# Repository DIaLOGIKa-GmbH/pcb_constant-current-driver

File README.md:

# LED Constant Current Driver Design

This project is part of [LibroDuct](https://www.libroduct.com/). We decided to publish some results of our LED driver designs to support the opensource maker scene. Feel free to use those results in your designs.

All those designs were tested with [9 IR-LEDs](https://jlcpcb.com/partdetail/Xssy-SE03_EMC3838AA60/C5205224) in series. These had a forward voltage of `14.0V`.

## LM3404 Constant Current Driver

The [LM3404 and LM3404HV](https://www.ti.com/lit/ds/symlink/lm3404.pdf) devices are monolithic switching regulators designed to deliver constant currents to high power LEDs. Ideal for automotive, industrial, and general lighting applications, these devices contain a high-side N-channel MOSFET switch with a current limit of 1.5A (typical) for step-down (Buck) regulators. Hysteretic controlled on-time and an external resistor allow the converter output voltage to adjust as needed to deliver a constant current to series and series-parallel connected LED arrays of varying number and type. 

_(LM3404 testing PCB render)_

The layout of the PCB closely resembles the recommended design shown in the datasheet.

_(LM3404 input and output current)_

As can be seen in this plot, the output current is not that stable when the input voltage is changed. This makes the chip unusable for applications with a varying input voltage.

_(LM3404 efficiency)_

TODO: Replace graph with better data. Chip seems to be quite efficient.

## AL8860 Constant Current Driver

The [AL8860](https://www.diodes.com/assets/Datasheets/AL8860.pdf) is a hysteresis mode DC-DC step-down converter, designed for driving single or multiple series connected LEDs efficiently from a voltage source higher than the LED voltage. The device can operate from an input supply between `4.5V` and `40V` and provide an externally adjustable output current up to `1A` for TSOT25 package and `1.5A` for MSOP-8EP package.

_(AL8860 testing PCB render)_

The curcuit designed is similar to the previous circuit but produces way better results thanks to the changed driving IC.

_(AL8860 input and output current)_

The above plot shows the input and output current. The output current is rather stable over the supported input voltage. This makes the circuit suitable for our needs.

It is also worth mentioning that the output current is a bit higher than the designed current. This is fine in our usecase but it is something to be aware of.

_(AL8860 driver efficiency at 700mA)_

### The Influence of Coil Selection

Another test we did with these drivers is so test and asses the influence of different coils on the efficiency. Especially the influence of the DC resistance.

_(AL8860 driver efficiency when tested with different coils)_

The above plot shows the same AL8860 driver that was used previously, but we added another coil in the mix. `v.A` uses a coil with a DC resistance of `98mΩ`, `v.B` has a DC resistance of `201mΩ`. The inductance of both coils is identical.

It can be seen that the efficiency drops with higher DC resistance as this energy is lost in the form of heat created. It is therefore reasonable to use a bigger and better coil if the space is not constrained.

### 1.5A Driver with AL8860MP

There is also an `1.5A` version available of the driving IC. I tested it as well and got really good results. It seems to be a bit more efficient than the `700mA` version. This could also be due to two LED strings being in parallel or the lower value of the shunt resistor.

_(AL8860MP driver efficiency at 1.5A)_

### Comparison

There are many off-the-shelf LED driver modules available. One of them, the [Meanwell LDD700LS](https://www.meanwell-web.com/content/files/pdfs/productPdfs/MW/LDD-l/ldd-l-spec.pdf) was used here as a refernce point. When supplied with `36V` at `700mA` and a LED forward voltage of `14V`, it seems to have an efficieny of `87%`. Even in our worst case scenario our driver is more efficient.

_(LDD700LS driver module efficiency [fig 3, page 4])_

### Trigger Signals

Since the dimming pin of most LED driver ICs is open drain with a limited voltage range, we need additional circuitry to get what we need. Also many ICs support analog dimming with values over 100% if the internal ref voltage is surpassed which forces us to use the internal pullup.

The following circuit achieves all of that, while also supporting trigger voltages as high as VCC of the LED board, while also making sure that pulling the input to ground still disables it.

By default this circuit turns the device on and has to be actively turned off.

_(PWM input modification schematic)_

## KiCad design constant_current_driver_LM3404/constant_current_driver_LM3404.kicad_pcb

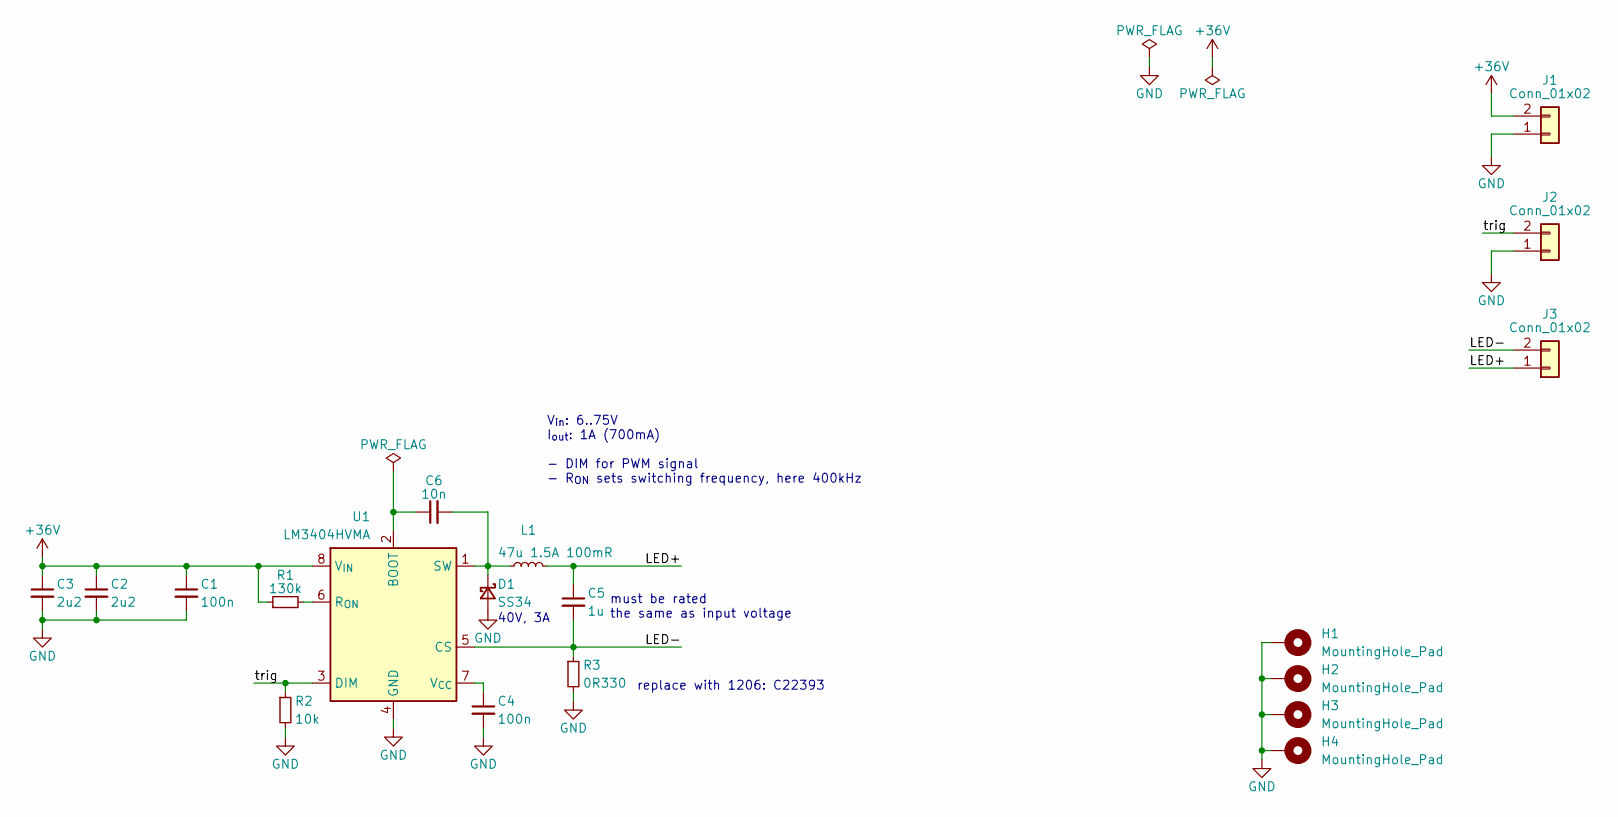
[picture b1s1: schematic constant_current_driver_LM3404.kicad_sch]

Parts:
C1, C4: 100n; C_0603_1608Metric; LCSC Part # C14663
C2, C3: 2u2; C_1206_3216Metric; LCSC Part # C50254
C5: 1u; C_1206_3216Metric; LCSC Part # C1848
C6: 10n; C_0603_1608Metric; LCSC Part # C57112
D1: SS34; D_SMA; LCSC Part # C8678
H1, H2, H3, H4: MountingHole_Pad; MountingHole_3.2mm_M3_Pad_TopOnly; LCSC Part # DNP
J1, J2, J3: Conn_01x02; TerminalBlock_Phoenix_MKDS-1,5-2-5.08_1x02_P5.08mm_Horizont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; LCSC Part # C8465
L1: 47u 1.5A 100mR; L_TDK_SLF10145; LCSC Part # C329816
R1: 130k; R_0603_1608Metric; LCSC Part # C22795
R2: 10k; R_0603_1608Metric; LCSC Part # C25804
R3: 0R330; R_0805_2012Metric; LCSC Part # C724024
U1: LM3404HVMA; SOIC-8_3.9x4.9mm_P1.27mm; LCSC Part # C1554286

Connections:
+36V: C1.1, C2.1, C3.1, J1.2, R1.1, U1.8 (V_{IN})
/LED+: C5.1, J3.1, L1.2
/LED-: C5.2, J3.2, R3.1, U1.5 (CS)
/trig: J2.2, R2.1, U1.3 (DIM)
GND: C1.2, C2.2, C3.2, C4.2, D1.2 (A), H1.1, H2.1, H3.1, H4.1, J1.1, J2.1, R2.2, R3.2, U1.4 (GND)
unnamed: C6.2, D1.1 (K), L1.1, U1.1 (SW)
unnamed: C6.1, U1.2 (BOOT)
unnamed: R1.2, U1.6 (R_{ON})
unnamed: C4.1, U1.7 (V_{CC})

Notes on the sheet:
must be rated the same as input voltage
40V, 3A
replace with 1206: C22393
V_{in}: 6..75V I_{out}: 1A (700mA) - DIM for PWM signal - R_{ON} sets switching frequency, here 400kHz

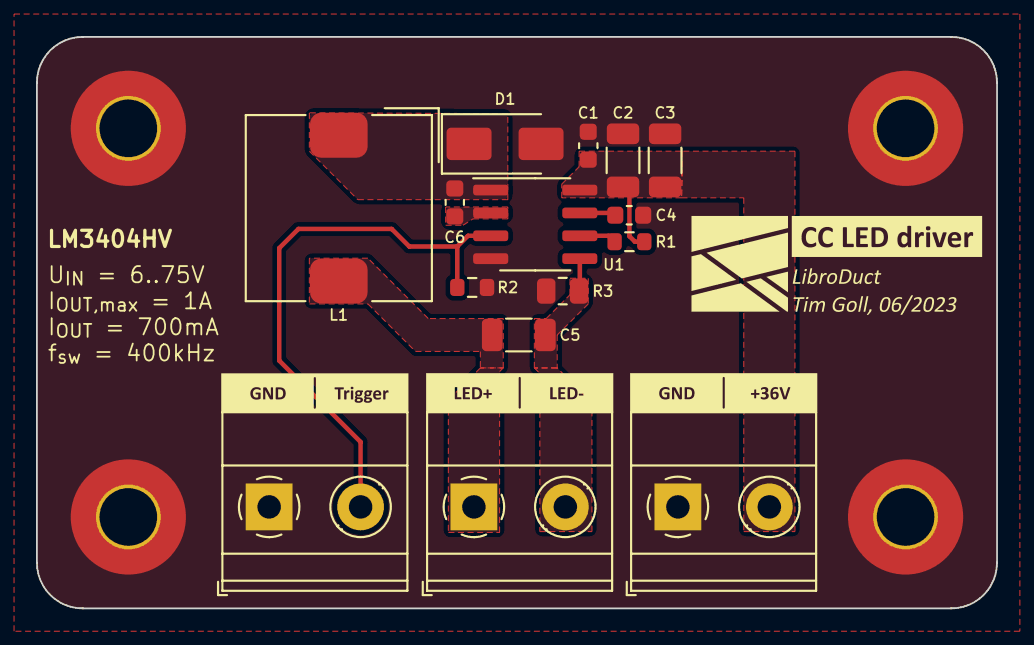
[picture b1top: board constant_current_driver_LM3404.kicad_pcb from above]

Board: 2 copper layers, 53.3 x 31.8 mm, 19 parts (0 on the bottom side), 9 nets.

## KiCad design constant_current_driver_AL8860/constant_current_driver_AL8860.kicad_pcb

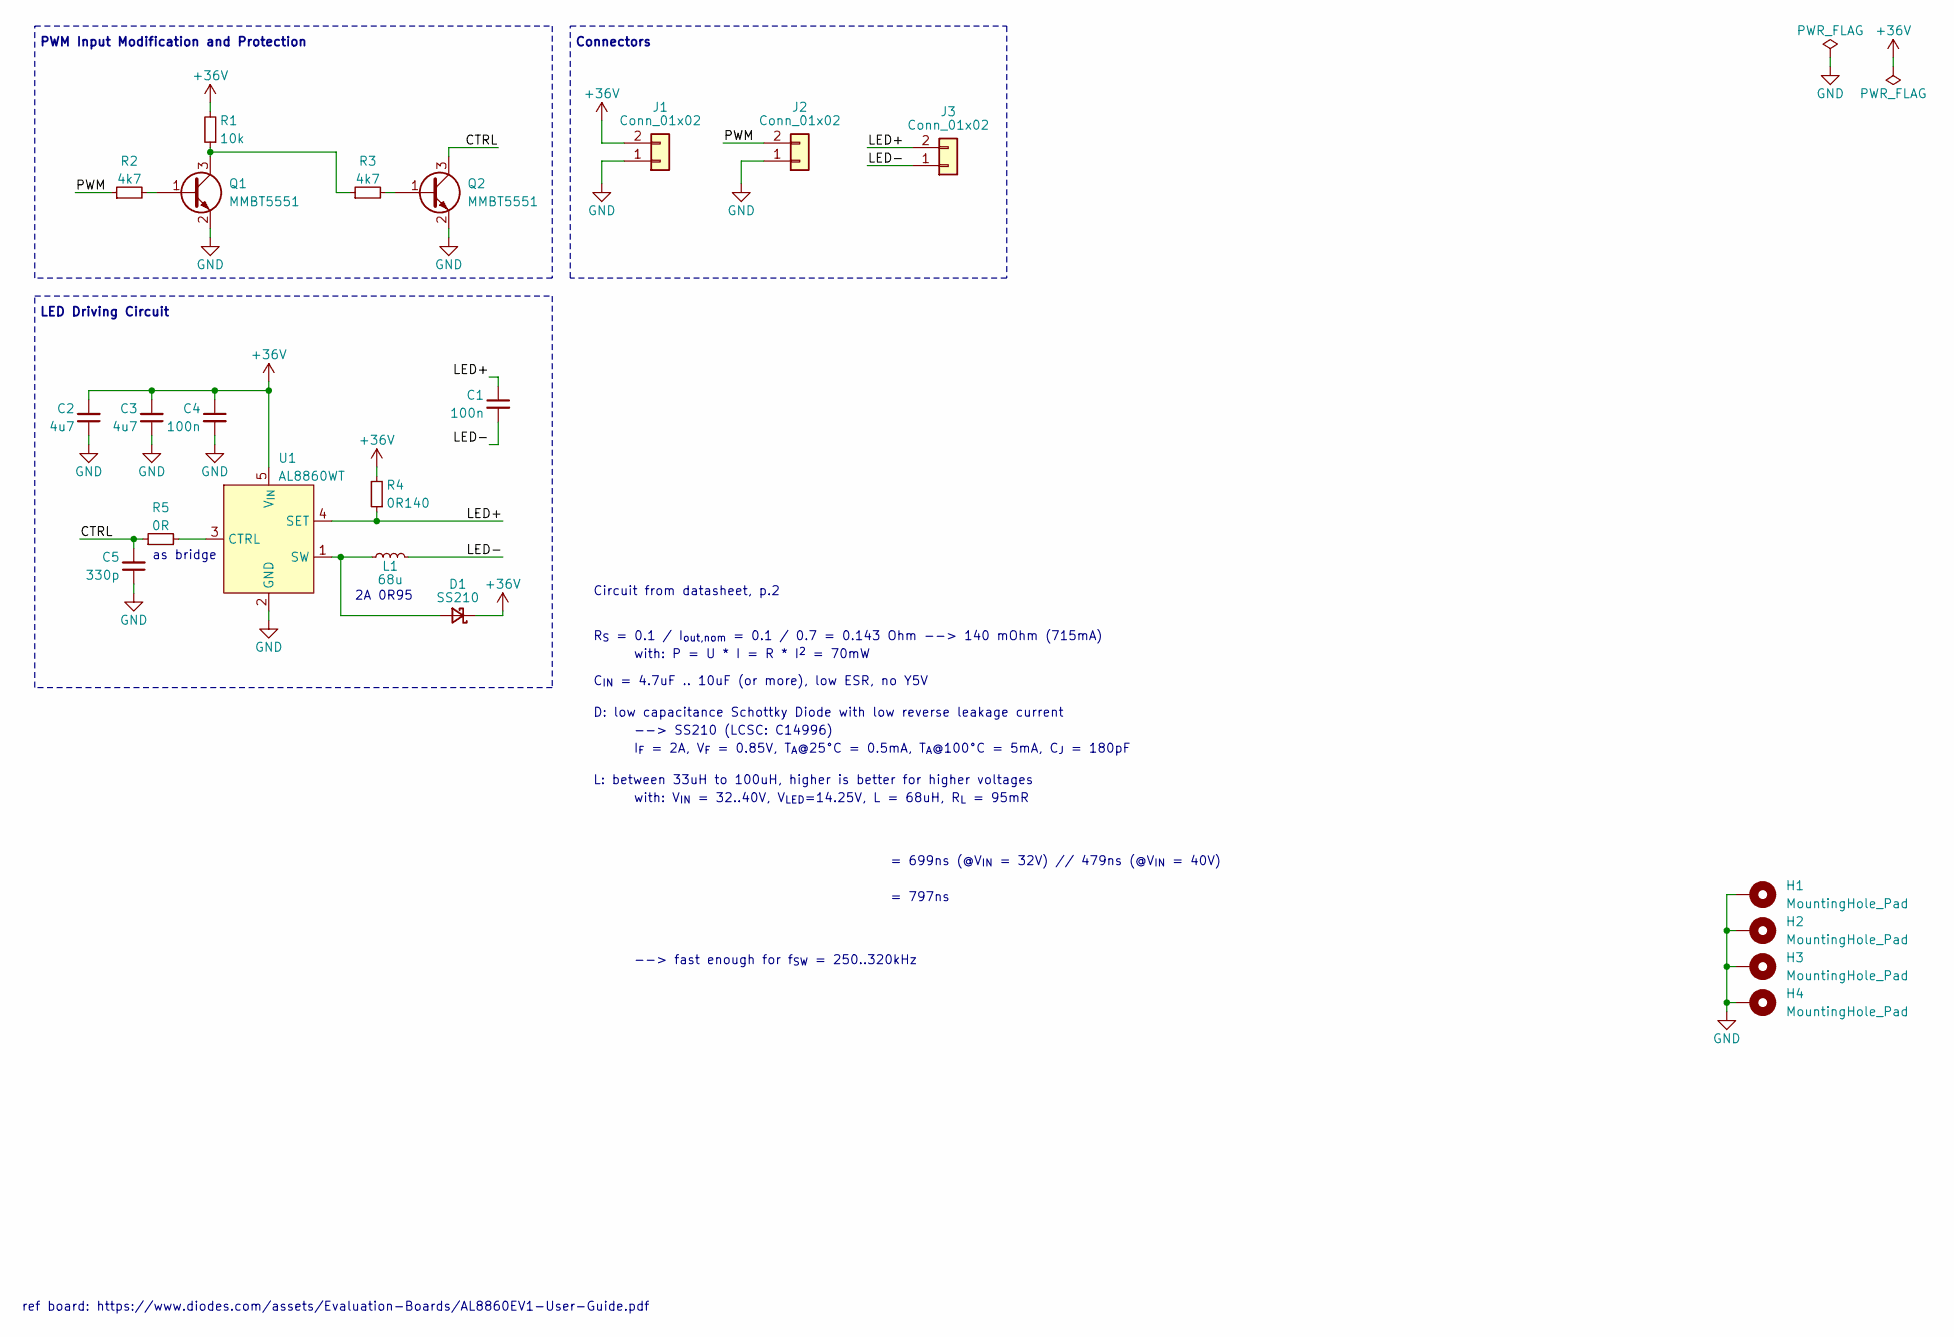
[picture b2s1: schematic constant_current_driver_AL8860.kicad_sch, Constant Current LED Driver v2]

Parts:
C1, C4: 100n; C_0603_1608Metric; LCSC Part # C14663
C2, C3: 4u7; C_1206_3216Metric; LCSC Part # C29823
C5: 330p; C_0402_1005Metric; LCSC Part # C13533
D1: SS210; D_SMA; LCSC Part # C14996
H1, H2, H3, H4: MountingHole_Pad; MountingHole_3.2mm_M3_Pad_TopOnly; LCSC Part # DNP
J1, J2, J3: Conn_01x02; TerminalBlock_Phoenix_MKDS-1,5-2-5.08_1x02_P5.08mm_Horizont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; LCSC Part # C8465
L1: 68u; L_TDK_SLF12565; LCSC Part # C693891
Q1, Q2: MMBT5551; TSOT-23; LCSC Part # C2145
R1: 10k; R_0402_1005Metric; LCSC Part # C25744
R2, R3: 4k7; R_0402_1005Metric; LCSC Part # C25900
R4: 0R140; R_1206_3216Metric; LCSC Part # C5138989
R5: 0R; R_1206_3216Metric; LCSC Part # C17888
U1: AL8860WT; TSOT-23-5; LCSC Part # C125330

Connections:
+36V: C2.2, C3.2, C4.1, D1.1 (K), J1.2, R1.2, R4.2, U1.5 (V_{IN})
/CTRL: C5.2, Q2.3 (C), R5.1
/LED+: C1.1, J3.2, R4.1, U1.4 (SET)
/LED-: C1.2, J3.1, L1.2
/PWM: J2.2, R2.1
GND: C2.1, C3.1, C4.2, C5.1, H1.1, H2.1, H3.1, H4.1, J1.1, J2.1, Q1.2 (E), Q2.2 (E), U1.2 (GND)
unnamed: D1.2 (A), L1.1, U1.1 (SW)
unnamed: Q1.1 (B), R2.2
unnamed: Q1.3 (C), R1.1, R3.1
unnamed: Q2.1 (B), R3.2
unnamed: R5.2, U1.3 (CTRL)

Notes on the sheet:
L: between 33uH to 100uH, higher is better for higher voltages
= 699ns (@V_{IN} = 32V) // 479ns (@V_{IN} = 40V)
R_{S} = 0.1 / I_{out,nom} = 0.1 / 0.7 = 0.143 Ohm --> 140 mOhm (715mA)
--> SS210 (LCSC: C14996)
as bridge
with: V_{IN} = 32..40V, V_{LED}=14.25V, L = 68uH, R_{L} = 95mR
2A 0R95
LED Driving Circuit
D: low capacitance Schottky Diode with low reverse leakage current
with: P = U * I = R * I^{2} = 70mW
I_{F} = 2A, V_{F} = 0.85V, T_{A}@25°C = 0.5mA, T_{A}@100°C = 5mA, C_{J} = 180pF
= 797ns
C_{IN} = 4.7uF .. 10uF (or more), low ESR, no Y5V
PWM Input Modification and Protection
--> fast enough for f_{SW} = 250..320kHz
Connectors
Circuit from datasheet, p.2
ref board: https://www.diodes.com/assets/Evaluation-Boards/AL8860EV1-User-Guide.pdf

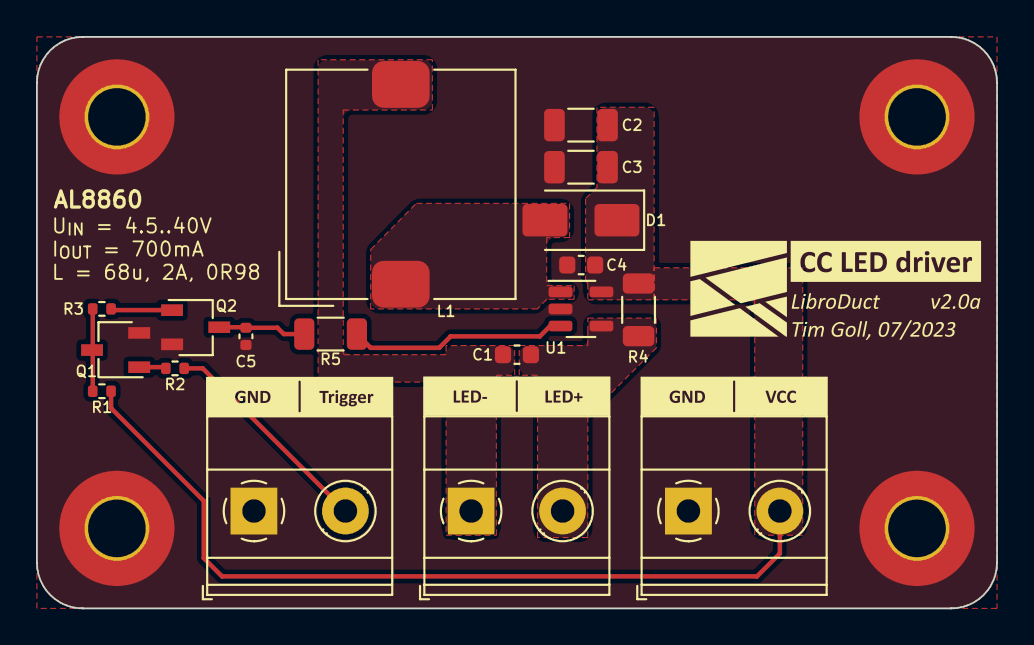
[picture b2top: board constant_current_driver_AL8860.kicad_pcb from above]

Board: 2 copper layers, 53.3 x 31.8 mm, 22 parts (0 on the bottom side), 11 nets.

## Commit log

2023-11-14 moved AL8860 LED driver to repository
2023-11-14 added data
2023-11-14 added LM3404 driver
2023-11-14 set project type
2023-11-14 added python to ignore list
2023-11-15 added documentation
2023-11-15 updated images
2023-11-15 renamed files
2023-11-15 made names upper case
2023-11-15 fixed typo
2023-11-20 fixed typo in docs
